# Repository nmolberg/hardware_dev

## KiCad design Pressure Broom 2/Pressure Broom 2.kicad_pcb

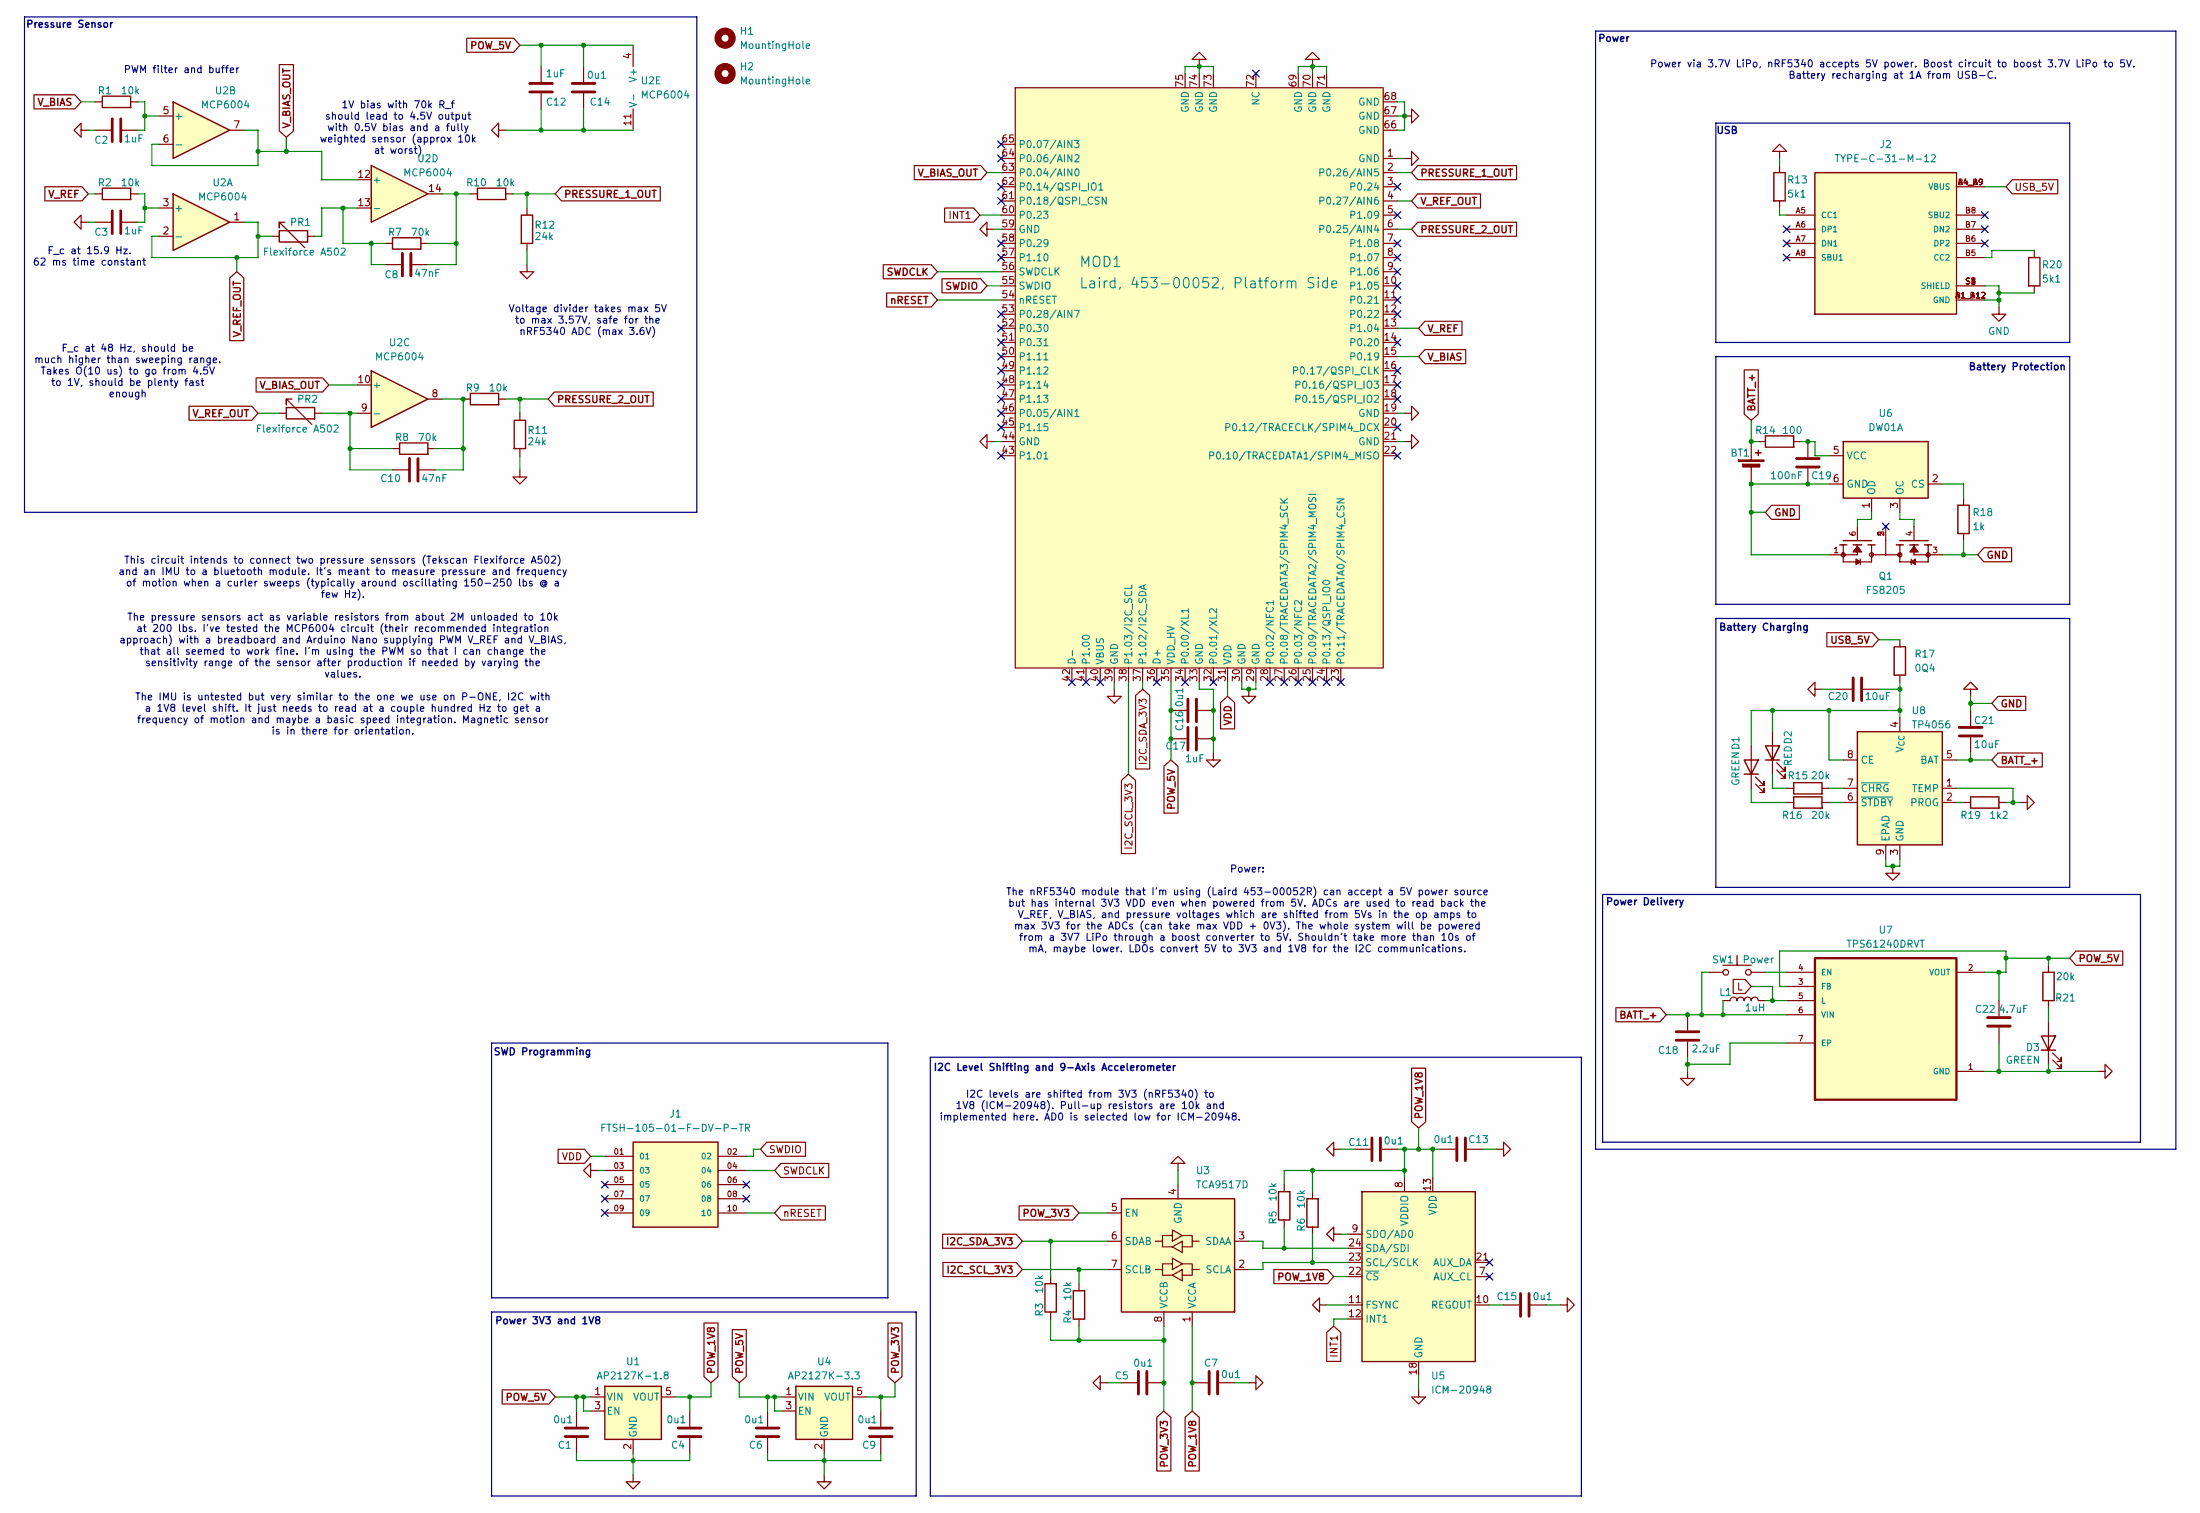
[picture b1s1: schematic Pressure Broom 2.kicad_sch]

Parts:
BT1: Battery_Cell; JST_PH_S2B-PH-K_1x02_P2.00mm_Horizontal
C1, C4, C5, C6, C7, C9, C11, C13, C14, C15: 0u1; C_0402_1005Metric
C2, C3, C12: 1uF; C_0402_1005Metric
C8, C10: 47nF; C_0402_1005Metric
C16: 0u1; C_0603_1608Metric
C17: 1uF; C_0603_1608Metric
C18: 2.2uF; C_0603_1608Metric
C19: 100nF; C_0603_1608Metric
C20, C21: 10uF; C_0603_1608Metric
C22: 4.7uF; C_0603_1608Metric
D1, D3: GREEN; LED_0402_1005Metric
D2: RED; LED_0402_1005Metric
H1, H2: MountingHole; MountingHole_2.2mm_M2
J1: FTSH-105-01-F-DV-P-TR; SAMTEC_FTSH-105-01-F-DV-P-TR; PARTREV R
J2: TYPE-C-31-M-12; HRO_TYPE-C-31-M-12; PARTREV 2020.12.08
L1: 1uH; L_0603_1608Metric; Part LQM21PN1R0MC0
MOD1: Laird, 453-00052, Platform Side; Ezurio Module; Manufacturer Part Number 453-00052
PR1, PR2: Flexiforce A502; Tekscan Pressure Sensor
Q1: FS8205; SOT95P280X145-6N; PARTREV 1.9
R1, R2, R3, R5, R9, R10: 10k; R_0402_1005Metric_Pad0.72x0.64mm_HandSolder
R4, R6: 10k; R_0603_1608Metric
R7, R8: 70k; R_0402_1005Metric_Pad0.72x0.64mm_HandSolder
R11, R12: 24k; R_0402_1005Metric_Pad0.72x0.64mm_HandSolder
R13, R20: 5k1; R_0402_1005Metric_Pad0.72x0.64mm_HandSolder
R14: 100; R_0402_1005Metric_Pad0.72x0.64mm_HandSolder
R15, R16, R21: 20k; R_0402_1005Metric_Pad0.72x0.64mm_HandSolder
R17: 0Q4; R_0402_1005Metric_Pad0.72x0.64mm_HandSolder
R18: 1k; R_0402_1005Metric_Pad0.72x0.64mm_HandSolder
R19: 1k2; R_0402_1005Metric_Pad0.72x0.64mm_HandSolder
SW1: Power; YTSPS-22E58LM
U1: AP2127K-1.8; SOT-23-5
U2: MCP6004; SOP65P640X120-14N
U3: TCA9517D; VSSOP-8_3x3mm_P0.65mm
U4: AP2127K-3.3; SOT-23-5
U5: ICM-20948; InvenSense_QFN-24_3x3mm_P0.4mm
U6: DW01A; SOT-23-6
U7: TPS61240DRVT
U8: TP4056; SOIC-8-1EP_3.9x4.9mm_P1.27mm_EP2.41x3.3mm_ThermalVias

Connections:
BATT_+: BT1.1 (+), C18.2, C21.2, L1.1, R14.1, SW1.1, U7.6 (VIN), U8.5 (BAT)
GND: BT1.2 (-), C1.1, C2.2, C3.2, C4.1, C5.2, C6.1, C7.1, C9.1, C11.2, C12.2, C13.2, C14.2, C15.2, C16.2, C17.2, C18.1, C19.2, C20.1, C21.1, C22.1, D3.1 (K), J1.03, J2.A1_B12 (GND), J2.B1_A12 (GND), J2.S1 (SHIELD), J2.S2 (SHIELD), J2.S3 (SHIELD), J2.S4 (SHIELD), MOD1.1 (GND), MOD1.19 (GND), MOD1.21 (GND), MOD1.29 (GND), MOD1.30 (GND), MOD1.33 (GND), MOD1.39 (GND), MOD1.44 (GND), MOD1.59 (GND), MOD1.66 (GND), MOD1.67 (GND), MOD1.68 (GND), MOD1.69 (GND), MOD1.70 (GND), MOD1.71 (GND), MOD1.73 (GND), MOD1.74 (GND), MOD1.75 (GND), Q1.1, Q1.3, R11.2, R12.2, R13.1, R18.2, R19.2, R20.2, U1.2 (GND), U2.11 (V-), U3.4 (GND), U4.2 (GND), U5.9 (SDO/AD0), U5.11 (FSYNC), U5.18 (GND), U5.20 (GND), U6.6 (GND), U7.1 (GND), U7.7 (EP), U8.1 (TEMP), U8.3 (GND), U8.9 (EPAD)
I2C_SCL_3V3: MOD1.38 (P1.03/I2C_SCL), R4.2, U3.7 (SCLB)
I2C_SDA_3V3: MOD1.37 (P1.02/I2C_SDA), R3.2, U3.6 (SDAB)
INT1: MOD1.60 (P0.23), U5.12 (INT1)
L: L1.2, U7.5 (L)
unnamed: C8.1, R7.2, R10.1, U2.14
unnamed: C10.1, R8.2, R9.1, U2.8
unnamed: C20.2, D1.2 (A), D2.2 (A), R17.2, U8.4 (V_{CC}), U8.8 (CE)
unnamed: D1.1 (K), R16.1
unnamed: D2.1 (K), R15.1
unnamed: D3.2 (A), R21.1
unnamed: J2.A5 (CC1), R13.2
unnamed: J2.B5 (CC2), R20.1
unnamed: C3.1, R2.2, U2.3 (+)
unnamed: C2.1, R1.2, U2.5 (+)
unnamed: C10.2, PR2.2, R8.1, U2.9 (-)
unnamed: C8.2, PR1.2, R7.1, U2.13 (-)
unnamed: R6.1, U3.2 (SCLA), U5.23 (SCL/SCLK)
unnamed: R5.1, U3.3 (SDAA), U5.24 (SDA/SDI)
unnamed: C15.1, U5.10 (REGOUT)
unnamed: R18.1, U6.2 (CS)
unnamed: Q1.4, U6.3 (OC)
unnamed: Q1.6, U6.1 (OD)
unnamed: C19.1, R14.2, U6.5 (VCC)
unnamed: SW1.2, U7.4 (EN)
unnamed: R19.1, U8.2 (PROG)
unnamed: R15.2, U8.7 (~CHRG)
unnamed: R16.2, U8.6 (~STDBY)
POW_1V8: C4.2, C7.2, C11.1, C13.1, R5.2, R6.2, U1.5 (VOUT), U3.1 (VCCA), U5.8 (VDDIO), U5.13 (VDD), U5.22 (~CS)
POW_3V3: C5.1, C9.2, R3.1, R4.1, U3.5 (EN), U3.8 (VCCB), U4.5 (VOUT)
POW_5V: C1.2, C6.2, C12.1, C14.1, C16.1, C17.1, C22.2, MOD1.35 (VDD_HV), R21.2, U1.1 (VIN), U1.3 (EN), U2.4 (V+), U4.1 (VIN), U4.3 (EN), U7.2 (VOUT), U7.3 (FB)
PRESSURE_1_OUT: MOD1.2 (P0.26/AIN5), R10.2, R12.1
PRESSURE_2_OUT: MOD1.6 (P0.25/AIN4), R9.2, R11.1
SWDCLK: J1.04, MOD1.56 (SWDCLK)
SWDIO: J1.02, MOD1.55 (SWDIO)
USB_5V: J2.A4_B9 (VBUS), J2.B4_A9 (VBUS), R17.1
VDD: J1.01, MOD1.31 (VDD)
V_BIAS: MOD1.15 (P0.19), R1.1
V_BIAS_OUT: MOD1.63 (P0.04/AIN0), U2.6 (-), U2.7, U2.10 (+), U2.12 (+)
V_REF: MOD1.13 (P1.04), R2.1
V_REF_OUT: MOD1.4 (P0.27/AIN6), PR1.1, PR2.1, U2.1, U2.2 (-)
nRESET: J1.10, MOD1.54 (nRESET)

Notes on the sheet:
Power
USB
Battery Charging
I2C Level Shifting and 9-Axis Accelerometer
Voltage divider takes max 5V to max 3.57V, safe for the nRF5340 ADC (max 3.6V)
1V bias with 70k R_f should lead to 4.5V output with 0.5V bias and a fully weighted sensor (approx 10k at worst)
Power Delivery
Power via 3.7V LiPo, nRF5340 accepts 5V power. Boost circuit to boost 3.7V LiPo to 5V. Battery recharging at 1A from USB-C.
This circuit intends to connect two pressure senssors (Tekscan Flexiforce A502) and an IMU to a bluetooth module. It's meant to measure pressure and frequency of motion when a curler sweeps (typically around oscillating 150-250 lbs @ a few Hz). The pressure sensors act as variable resistors from ab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
Pressure Sensor
Power 3V3 and 1V8
F_c at 48 Hz, should be much higher than sweeping range. Takes O(10 us) to go from 4.5V to 1V, should be plenty fast enough
F_c at 15.9 Hz. 62 ms time constant
PWM filter and buffer
I2C levels are shifted from 3V3 (nRF5340) to 1V8 (ICM-20948). Pull-up resistors are 10k and implemented here. AD0 is selected low for ICM-20948.
Battery Protection
SWD Programming
Power: The nRF5340 module that I'm using (Laird 453-00052R) can accept a 5V power source but has internal 3V3 VDD even when powered from 5V. ADCs are used to read back the V_REF, V_BIAS, and pressure voltages which are shifted from 5Vs in the op amps to max 3V3 for the ADCs (can take max VDD + 0V3)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

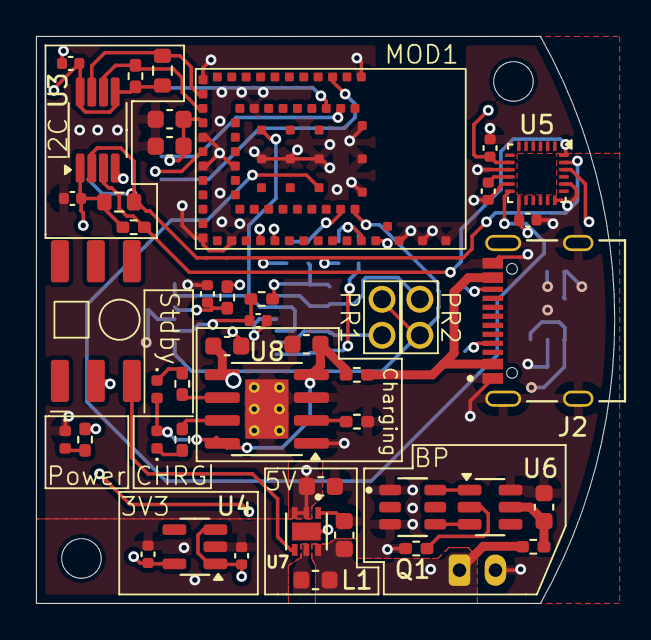
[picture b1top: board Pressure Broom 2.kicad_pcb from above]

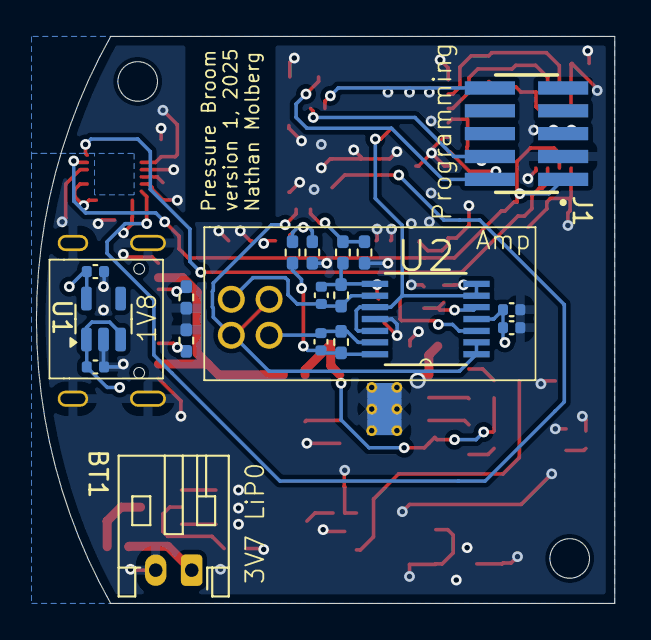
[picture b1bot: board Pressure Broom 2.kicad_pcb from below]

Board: 4 copper layers, 32.1 x 31.5 mm, 65 parts (18 on the bottom side), 43 nets.

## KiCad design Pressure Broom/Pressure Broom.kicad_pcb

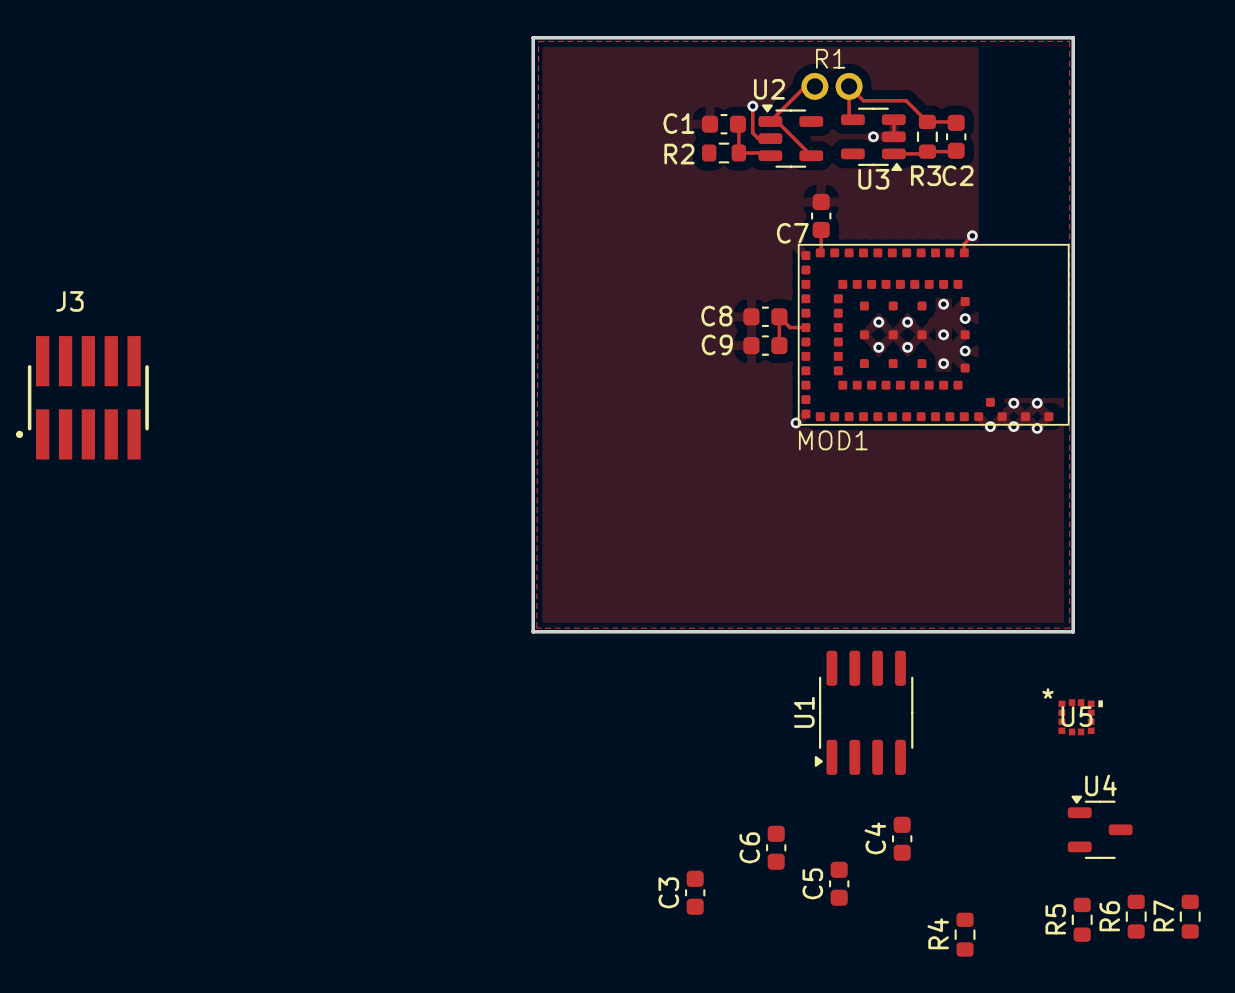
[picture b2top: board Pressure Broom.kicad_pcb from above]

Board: 2 copper layers, 30.0 x 33.0 mm, 23 parts (0 on the bottom side), 17 nets.

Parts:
C1: 470pF; C_0603_1608Metric
C2: 47pF; C_0603_1608Metric
C3, C5: 100nF; C_0603_1608Metric
C4, C9: 10uF; C_0603_1608Metric
C6: 220nF; C_0603_1608Metric
C7: 4.7uF; C_0603_1608Metric
C8: 0.1uF; C_0603_1608Metric
J3: FTSH-105-01-S-DV-TR; SAMTEC_FTSH-105-01-S-DV-TR
MOD1: Laird, 453-00053, Platform Side; Ezurio Module
R1: Flexiforce A502; Untitled
R2, R4, R5, R6, R7: 10k; R_0603_1608Metric
R3: R; R_0603_1608Metric
U1: TCA9517D; SOIC-8_3.9x4.9mm_P1.27mm
U2, U3: MCP6001-OT; SOT-23-5
U4: MCP1700x-180xxTT; SOT-23-3
U5: ISM303DACTR; LGA_DACTR_STM

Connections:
GND: C1.2, C3.2, C4.2, C5.1, C6.2, C7.2, C8.1, C9.1, J3.03, J3.05, MOD1.1 (GND), MOD1.19 (GND), MOD1.21 (GND), MOD1.29 (GND), MOD1.30 (GND), MOD1.33 (GND), MOD1.39 (GND), MOD1.44 (GND), MOD1.59 (GND), MOD1.66 (GND), MOD1.67 (GND), MOD1.68 (GND), MOD1.69 (GND), MOD1.70 (GND), MOD1.71 (GND), MOD1.73 (GND), MOD1.74 (GND), MOD1.75 (GND), U1.4 (GND), U2.2 (V-), U3.2 (V-), U3.3 (+), U4.1 (GND), U5.3 (RESERVED), U5.6 (GND), U5.8 (GND)
I2C_SCL_1V8: C3.1, C4.1, C5.2, R6.1, R6.2, R7.1, U1.1 (VCCA), U1.2 (SCLA), U4.2 (VO), U5.1 (SCL/SPC), U5.2 (CS), U5.9 (VDD), U5.10 (VDD_IO)
I2C_SCL_3V3: MOD1.38 (P1.03/I2C_SCL), R4.2, U1.7 (SCLB)
I2C_SDA_1V8: R7.2, U1.3 (SDAA), U5.4 (SDA/SDI/SDO)
I2C_SDA_3V3: MOD1.37 (P1.02/I2C_SDA), R5.2, U1.6 (SDAB)
unnamed: C1.1, R2.2, U2.3 (+)
unnamed: C2.1, R1.1, R3.1, U3.4 (-)
unnamed: C6.1, U5.5 (C1)
PWM_0V5: MOD1.47 (P1.13), R2.1
PressureOut: C2.2, MOD1.53 (P0.28/AIN7), R3.2, U3.1
SWDCLK: J3.04, MOD1.56 (SWDCLK)
SWDIO: J3.02, MOD1.55 (SWDIO)
USB_POWER_5V: C7.1, MOD1.40 (VBUS)
VDD: C8.2, C9.2, J3.01, MOD1.31 (VDD), MOD1.35 (VDD_HV)
VRef_0V5: MOD1.46 (P0.05/AIN1), R1.2, U2.1, U2.4 (-)
VSupply3V3: R4.1, R5.1, U1.8 (VCCB), U2.5 (V+), U3.5 (V+), U4.3 (VI)
nRESET: J3.10, MOD1.54 (nRESET)

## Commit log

2025-07-15 Add datasheets and correct project
2025-07-15 Add project files?
2025-07-15 Documentation and Flexiforce datasheets
